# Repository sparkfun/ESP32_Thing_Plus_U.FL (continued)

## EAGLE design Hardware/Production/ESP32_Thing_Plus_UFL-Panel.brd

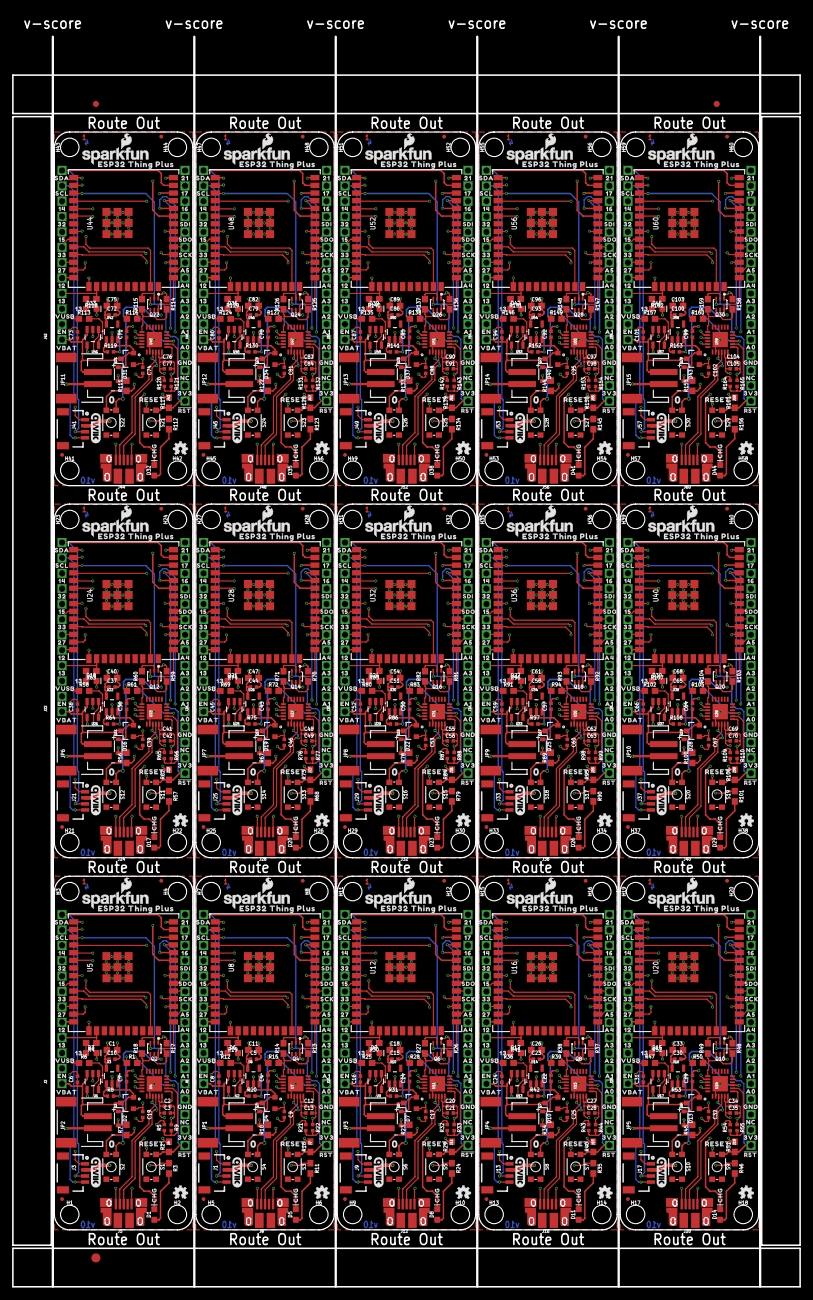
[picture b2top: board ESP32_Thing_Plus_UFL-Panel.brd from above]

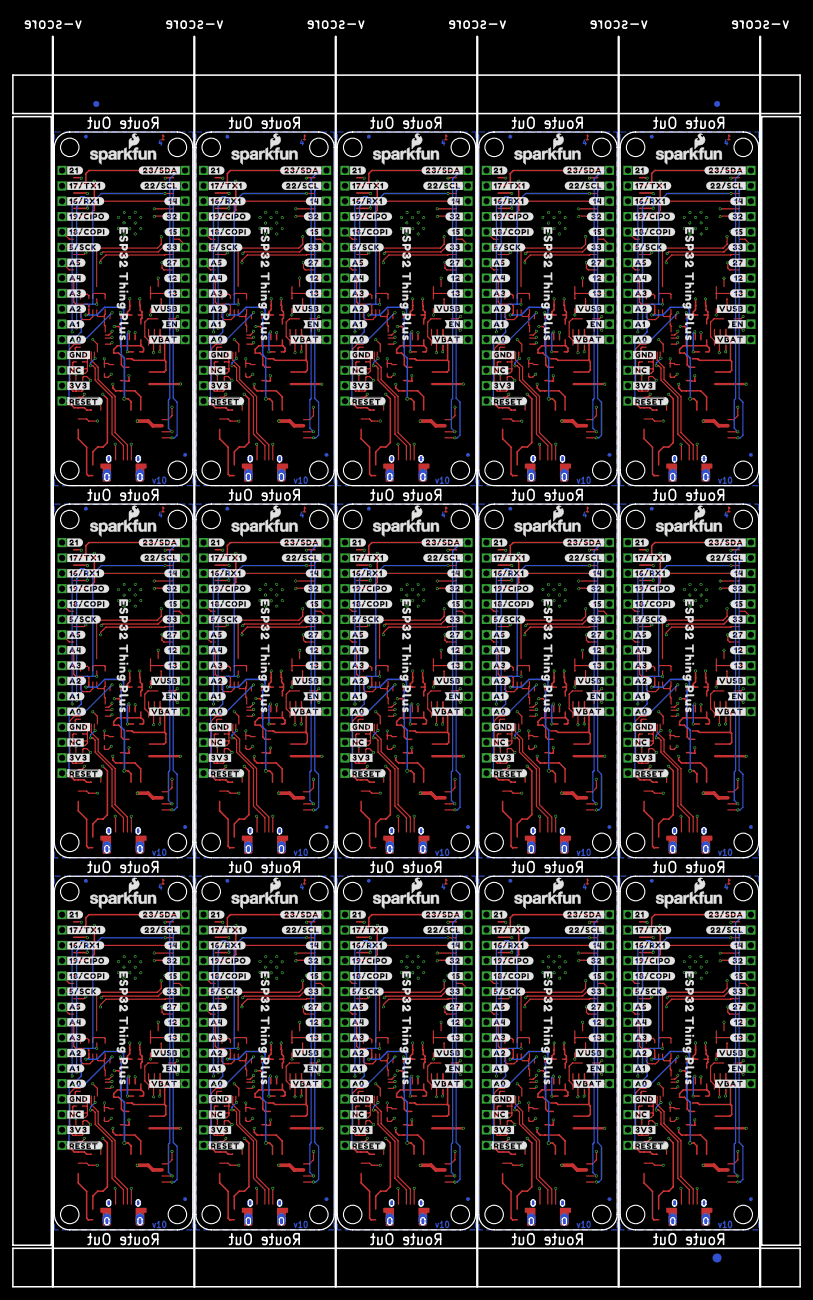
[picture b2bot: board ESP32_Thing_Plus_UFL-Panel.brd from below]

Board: 4 copper layers, 130.0 x 206.5 mm, 1671 parts (483 on the bottom side), 645 nets.

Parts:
C1, C11, C18, C26, C33, C40, C47, C54, C61, C68, C75, C82, C89, C96, C103: 10uF; 0603
C2, C12, C20, C27, C34, C41, C48, C55, C62, C69, C76, C83, C90, C97, C104: 0.1uF; 0402-TIGHT
C3, C6, C8, C9, C13, C16, C17, C19, C21, C24, C25, C28, C31, C32, C35, C38, C39, C42, C45, C46, C49, C52, C53, C56, C59, C60, C63, C66, C67, C70, C73, C74, C77, C80, C81, C84, C87, C88, C91, C94, C95, C98, C101, C102, C105: 4.7uF; 0402-TIGHT
C4, C5, C7, C10, C14, C15, C22, C23, C29, C30, C36, C37, C43, C44, C50, C51, C57, C58, C64, C65, C71, C72, C78, C79, C85, C86, C92, C93, C99, C100: 1.0uF; 0402-TIGHT
D1, D5, D8, D11, D14, D17, D20, D23, D26, D29, D32, D35, D38, D41, D44: Yellow; LED-0603
D2, D4, D7, D10, D13, D16, D19, D22, D25, D28, D31, D34, D37, D40, D43: 1A/23V/620mV; SOD-323
D3, D6, D9, D12, D15, D18, D21, D24, D27, D30, D33, D36, D39, D42, D45: BLUE; LED-0603
E$1, E$2, E$3, E$4: FIDUCIAL-1X2
E$5, E$6: FIDUCIAL-1.5X3
FD1, FD2, FD3, FD4, FD5, FD6, FD7, FD8, FD9, FD10, FD11, FD12, FD13, FD14, FD15, FD16, FD17, FD18, FD19, FD20, FD21, FD22, FD23, FD24, FD25, FD26, FD27, FD28, FD29, FD30, FD31, FD32, FD33, FD34, FD35, FD36, FD37, FD38, FD39, FD40, FD41, FD42, FD43, FD44, FD45, FD46, FD47, FD48, FD49, FD50, FD51, FD52, FD53, FD54, FD55, FD56, FD57, FD58, FD59, FD60: FIDUCIALUFIDUCIAL; FIDUCIAL-MICRO
H1, H2, H3, H4, H5, H6, H7, H8, H9, H10, H11, H12, H13, H14, H15, H16, H17, H18, H19, H20, H21, H22, H23, H24, H25, H26, H27, H28, H29, H30, H31, H32, H33, H34, H35, H36, H37, H38, H39, H40, H41, H42, H43, H44, H45, H46, H47, H48, H49, H50, H51, H52, H53, H54, H55, H56, H57, H58, H59, H60: STAND-OFFTIGHT; STAND-OFF-TIGHT
J1, J3, J9, J13, J17, J21, J25, J29, J33, J37, J41, J45, J49, J53, J57: 1X04_1MM_RA
J2, J6, J10, J14, J18, J22, J26, J30, J34, J38, J42, J46, J50, J54, J58: 1X12_SM_SQ_NOSILK
J4, J7, J11, J15, J19, J23, J27, J31, J35, J39, J43, J47, J51, J55, J59: 1X16_SM_SQ_NOSILK
J5, J8, J12, J16, J20, J24, J28, J32, J36, J40, J44, J48, J52, J56, J60: USB-MICROB-PTH-MILL
JP1, JP2, JP3, JP4, JP5, JP6, JP7, JP8, JP9, JP10, JP11, JP12, JP13, JP14, JP15: LiPo; JST-2-SMD
LOGO1, LOGO2, LOGO11, LOGO16, LOGO21, LOGO26, LOGO31, LOGO36, LOGO41, LOGO46, LOGO51, LOGO56, LOGO61, LOGO66, LOGO71: OSHW-LOGOMINI; OSHW-LOGO-MINI
LOGO3, LOGO5, LOGO7, LOGO9, LOGO12, LOGO14, LOGO17, LOGO19, LOGO22, LOGO24, LOGO27, LOGO29, LOGO32, LOGO34, LOGO37, LOGO39, LOGO42, LOGO44, LOGO47, LOGO49, LOGO52, LOGO54, LOGO57, LOGO59, LOGO62, LOGO64, LOGO67, LOGO69, LOGO72, LOGO74: SFE_LOGO_NAME_FLAME.1_INCH; SFE_LOGO_NAME_FLAME_.1
LOGO4, LOGO8, LOGO13, LOGO18, LOGO23, LOGO28, LOGO33, LOGO38, LOGO43, LOGO48, LOGO53, LOGO58, LOGO63, LOGO68, LOGO73: FOUR_LAYER_WARNING
LOGO6, LOGO10, LOGO15, LOGO20, LOGO25, LOGO30, LOGO35, LOGO40, LOGO45, LOGO50, LOGO55, LOGO60, LOGO65, LOGO70, LOGO75: QWIIC_LOGO_5MM; QWIIC_5MM
Q1, Q3, Q5, Q7, Q9, Q11, Q13, Q15, Q17, Q19, Q21, Q23, Q25, Q27, Q29: 2.5A/30V; SOT23-3@1
Q2, Q4, Q6, Q8, Q10, Q12, Q14, Q16, Q18, Q20, Q22, Q24, Q26, Q28, Q30: MBT3904DW1T1; SC70-6
R1, R2, R7, R10, R13, R14, R15, R16, R17, R18, R23, R26, R27, R28, R29, R34, R37, R38, R39, R40, R45, R48, R49, R50, R51, R56, R59, R60, R61, R62, R67, R70, R71, R72, R73, R78, R81, R82, R83, R84, R89, R92, R93, R94, R95, R100, R103, R104, R105, R106, R111, R114, R115, R116, R117, R122, R125, R126, R127, R128, R133, R136, R137, R138, R139, R144, R147, R148, R149, R150, R155, R158, R159, R160, R161: 10k; 0603
R3, R11, R24, R35, R46, R57, R68, R79, R90, R101, R112, R123, R134, R145, R156: 1K; 0603
R4, R19, R30, R41, R52, R63, R74, R85, R96, R107, R118, R129, R140, R151, R162: 1k; 0603
R5, R21, R32, R43, R54, R65, R76, R87, R98, R109, R120, R131, R142, R153, R164: 22k; 0402-TIGHT
R6, R12, R25, R36, R47, R58, R69, R80, R91, R102, R113, R124, R135, R146, R157: 2.0k; 0603
R8, R20, R31, R42, R53, R64, R75, R86, R97, R108, R119, R130, R141, R152, R163: 100k; 0402-TIGHT
R9, R22, R33, R44, R55, R66, R77, R88, R99, R110, R121, R132, R143, R154, R165: 33k; 0402-TIGHT
S1, S3, S5, S7, S9, S11, S13, S15, S17, S19, S21, S23, S25, S27, S29: RESET; TACTILE_SWITCH_SMD_4.6X2.8MM
S2, S4, S6, S8, S10, S12, S14, S16, S18, S20, S22, S24, S26, S28, S30: 0; TACTILE_SWITCH_SMD_4.6X2.8MM
TP1, TP2, TP3, TP4, TP5, TP6, TP7, TP8, TP9, TP10, TP11, TP12, TP13, TP14, TP15: TP_15TH
U1, U2, U9, U13, U17, U21, U25, U29, U33, U37, U41, U45, U49, U53, U57: MCP73831; SOT23-5
U3, U6, U10, U14, U18, U22, U26, U30, U34, U38, U42, U46, U50, U54, U58: AP2112K-3.3V; SOT23-5
U4, U7, U11, U15, U19, U23, U27, U31, U35, U39, U43, U47, U51, U55, U59: CP210X; QFN24
U5, U8, U12, U16, U20, U24, U28, U32, U36, U40, U44, U48, U52, U56, U60: ESP-WROOM-32EU; ESP-WROOM-32EU-NARROW
U$1, U$123, U$186, U$249, U$312, U$375, U$438, U$501, U$564, U$627, U$690, U$753, U$816, U$879, U$942: ESP32_THING_PLUS_0
U$2, U$124, U$187, U$250, U$313, U$376, U$439, U$502, U$565, U$628, U$691, U$754, U$817, U$880, U$943: SDI0
U$3, U$107, U$170, U$233, U$296, U$359, U$422, U$485, U$548, U$611, U$674, U$737, U$800, U$863, U$926: #21#0
U$4, U$108, U$171, U$234, U$297, U$360, U$423, U$486, U$549, U$612, U$675, U$738, U$801, U$864, U$927: #17#TX1#0
U$5, U$109, U$172, U$235, U$298, U$361, U$424, U$487, U$550, U$613, U$676, U$739, U$802, U$865, U$928: #16#RX1#0
U$6, U$125, U$188, U$251, U$314, U$377, U$440, U$503, U$566, U$629, U$692, U$755, U$818, U$881, U$944: SDO0
U$7, U$126, U$189, U$252, U$315, U$378, U$441, U$504, U$567, U$630, U$693, U$756, U$819, U$882, U$945: #RST#0
U$8, U$110, U$173, U$236, U$299, U$362, U$425, U$488, U$551, U$614, U$677, U$740, U$803, U$866, U$929: #19#CIPO#0
U$9, U$59, U$127, U$190, U$253, U$316, U$379, U$442, U$505, U$568, U$631, U$694, U$757, U$820, U$883: ORDERING_INSTRUCTIONS
U$10, U$111, U$174, U$237, U$300, U$363, U$426, U$489, U$552, U$615, U$678, U$741, U$804, U$867, U$930: #18#COPI#0
U$11, U$112, U$175, U$238, U$301, U$364, U$427, U$490, U$553, U$616, U$679, U$742, U$805, U$868, U$931: #5#SCK#0
U$12, U$113, U$176, U$239, U$302, U$365, U$428, U$491, U$554, U$617, U$680, U$743, U$806, U$869, U$932: #A5#0
U$13, U$24, U$128, U$191, U$254, U$317, U$380, U$443, U$506, U$569, U$632, U$695, U$758, U$821, U$884: ESP32_THING_PLUS0
U$14, U$25, U$129, U$192, U$255, U$318, U$381, U$444, U$507, U$570, U$633, U$696, U$759, U$822, U$885: SDA0
U$15, U$26, U$130, U$193, U$256, U$319, U$382, U$445, U$508, U$571, U$634, U$697, U$760, U$823, U$886: SCL0
U$16, U$58, U$131, U$194, U$257, U$320, U$383, U$446, U$509, U$572, U$635, U$698, U$761, U$824, U$887: 140
U$17, U$68, U$132, U$195, U$258, U$321, U$384, U$447, U$510, U$573, U$636, U$699, U$762, U$825, U$888: 320
U$18, U$69, U$133, U$196, U$259, U$322, U$385, U$448, U$511, U$574, U$637, U$700, U$763, U$826, U$889: 150
U$19, U$114, U$177, U$240, U$303, U$366, U$429, U$492, U$555, U$618, U$681, U$744, U$807, U$870, U$933: #A4#0
U$20, U$70, U$134, U$197, U$260, U$323, U$386, U$449, U$512, U$575, U$638, U$701, U$764, U$827, U$890: 330
U$21, U$115, U$178, U$241, U$304, U$367, U$430, U$493, U$556, U$619, U$682, U$745, U$808, U$871, U$934: #A3#0
U$22, U$116, U$179, U$242, U$305, U$368, U$431, U$494, U$557, U$620, U$683, U$746, U$809, U$872, U$935: #A2#0
U$23, U$71, U$135, U$198, U$261, U$324, U$387, U$450, U$513, U$576, U$639, U$702, U$765, U$828, U$891: 270
U$27, U$117, U$180, U$243, U$306, U$369, U$432, U$495, U$558, U$621, U$684, U$747, U$810, U$873, U$936: #A1#0
U$28, U$118, U$181, U$244, U$307, U$370, U$433, U$496, U$559, U$622, U$685, U$748, U$811, U$874, U$937: #A0#0
U$29, U$72, U$136, U$199, U$262, U$325, U$388, U$451, U$514, U$577, U$640, U$703, U$766, U$829, U$892: 120
U$30, U$47, U$73, U$74, U$137, U$138, U$200, U$201, U$263, U$264, U$326, U$327, U$389, U$390, U$452, U$453, U$515, U$516, U$578, U$579, U$641, U$642, U$704, U$705, U$767, U$768, U$830, U$831, U$893, U$894: 130
U$31, U$91, U$158, U$221, U$284, U$347, U$410, U$473, U$536, U$599, U$662, U$725, U$788, U$851, U$914: #23#SDA#0
U$32, U$119, U$182, U$245, U$308, U$371, U$434, U$497, U$560, U$623, U$686, U$749, U$812, U$875, U$938: #GND#0
U$33, U$92, U$159, U$222, U$285, U$348, U$411, U$474, U$537, U$600, U$663, U$726, U$789, U$852, U$915: #22#SCL#0
U$34, U$97, U$160, U$223, U$286, U$349, U$412, U$475, U$538, U$601, U$664, U$727, U$790, U$853, U$916: #14#0
U$35, U$98, U$161, U$224, U$287, U$350, U$413, U$476, U$539, U$602, U$665, U$728, U$791, U$854, U$917: #32#0
U$36, U$99, U$162, U$225, U$288, U$351, U$414, U$477, U$540, U$603, U$666, U$729, U$792, U$855, U$918: #15#0
U$37, U$100, U$163, U$226, U$289, U$352, U$415, U$478, U$541, U$604, U$667, U$730, U$793, U$856, U$919: #33#0
U$38, U$101, U$164, U$227, U$290, U$353, U$416, U$479, U$542, U$605, U$668, U$731, U$794, U$857, U$920: #27#0
U$39, U$102, U$165, U$228, U$291, U$354, U$417, U$480, U$543, U$606, U$669, U$732, U$795, U$858, U$921: #12#0
U$40, U$103, U$166, U$229, U$292, U$355, U$418, U$481, U$544, U$607, U$670, U$733, U$796, U$859, U$922: #13#0
U$41, U$104, U$167, U$230, U$293, U$356, U$419, U$482, U$545, U$608, U$671, U$734, U$797, U$860, U$923: #VUSB#0
U$42, U$105, U$168, U$231, U$294, U$357, U$420, U$483, U$546, U$609, U$672, U$735, U$798, U$861, U$924: #VBAT#0
U$43, U$106, U$169, U$232, U$295, U$358, U$421, U$484, U$547, U$610, U$673, U$736, U$799, U$862, U$925: #EN#0
U$44, U$120, U$183, U$246, U$309, U$372, U$435, U$498, U$561, U$624, U$687, U$750, U$813, U$876, U$939: #NC#0
U$45, U$121, U$184, U$247, U$310, U$373, U$436, U$499, U$562, U$625, U$688, U$751, U$814, U$877, U$940: #3V3#0
U$46, U$122, U$185, U$248, U$311, U$374, U$437, U$500, U$563, U$626, U$689, U$752, U$815, U$878, U$941: ##RESET##0
U$48, U$75, U$139, U$202, U$265, U$328, U$391, U$454, U$517, U$580, U$643, U$706, U$769, U$832, U$895: VUSB0
U$49, U$76, U$140, U$203, U$266, U$329, U$392, U$455, U$518, U$581, U$644, U$707, U$770, U$833, U$896: EN0
U$50, U$77, U$141, U$204, U$267, U$330, U$393, U$456, U$519, U$582, U$645, U$708, U$771, U$834, U$897: VBAT0
U$51, U$78, U$142, U$205, U$268, U$331, U$394, U$457, U$520, U$583, U$646, U$709, U$772, U$835, U$898: CHG0
U$52, U$79, U$143, U$206, U$269, U$332, U$395, U$458, U$521, U$584, U$647, U$710, U$773, U$836, U$899: RESET0
U$53, U$81, U$144, U$207, U$270, U$333, U$396, U$459, U$522, U$585, U$648, U$711, U$774, U$837, U$900: 3V30
U$54, U$82, U$145, U$208, U$271, U$334, U$397, U$460, U$523, U$586, U$649, U$712, U$775, U$838, U$901: NC0
U$55, U$83, U$146, U$209, U$272, U$335, U$398, U$461, U$524, U$587, U$650, U$713, U$776, U$839, U$902: GND0
U$56, U$84, U$147, U$210, U$273, U$336, U$399, U$462, U$525, U$588, U$651, U$714, U$777, U$840, U$903: A00
U$57, U$85, U$148, U$211, U$274, U$337, U$400, U$463, U$526, U$589, U$652, U$715, U$778, U$841, U$904: A10
U$60, U$86, U$149, U$212, U$275, U$338, U$401, U$464, U$527, U$590, U$653, U$716, U$779, U$842, U$905: A20
U$61, U$87, U$150, U$213, U$276, U$339, U$402, U$465, U$528, U$591, U$654, U$717, U$780, U$843, U$906: A30
U$62, U$88, U$151, U$214, U$277, U$340, U$403, U$466, U$529, U$592, U$655, U$718, U$781, U$844, U$907: A40
U$63, U$89, U$152, U$215, U$278, U$341, U$404, U$467, U$530, U$593, U$656, U$719, U$782, U$845, U$908: A50
U$64, U$90, U$153, U$216, U$279, U$342, U$405, U$468, U$531, U$594, U$657, U$720, U$783, U$846, U$909: SCK0
U$65, U$93, U$154, U$217, U$280, U$343, U$406, U$469, U$532, U$595, U$658, U$721, U$784, U$847, U$910: 160
U$66, U$94, U$155, U$218, U$281, U$344, U$407, U$470, U$533, U$596, U$659, U$722, U$785, U$848, U$911: 170
U$67, U$95, U$156, U$219, U$282, U$345, U$408, U$471, U$534, U$597, U$660, U$723, U$786, U$849, U$912: 210
U$80, U$96, U$157, U$220, U$283, U$346, U$409, U$472, U$535, U$598, U$661, U$724, U$787, U$850, U$913: 00

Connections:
0: Q2.6, S2.4, TP1.P$1, U5.25
1: Q4.6, S4.4, TP2.P$1, U8.25
2: J6.10, U8.13
3: J6.9, U8.8
3.3V: C1.1, C2.1, C3.1, C10.1, J3.2, J4.2, R1.1, R2.2, U3.5, U4.5, U4.6, U4.7, U5.2
3.3V1: C5.1, C11.1, C12.1, C13.1, J1.2, J7.2, R15.1, R16.2, U6.5, U7.5, U7.6, U7.7, U8.2
3.3V2: C15.1, C18.1, C20.1, C21.1, J9.2, J11.2, R28.1, R29.2, U10.5, U11.5, U11.6, U11.7, U12.2
3.3V3: C23.1, C26.1, C27.1, C28.1, J13.2, J15.2, R39.1, R40.2, U14.5, U15.5, U15.6, U15.7, U16.2
3.3V4: C30.1, C33.1, C34.1, C35.1, J17.2, J19.2, R50.1, R51.2, U18.5, U19.5, U19.6, U19.7, U20.2
3.3V5: C37.1, C40.1, C41.1, C42.1, J21.2, J23.2, R61.1, R62.2, U22.5, U23.5, U23.6, U23.7, U24.2
3.3V6: C44.1, C47.1, C48.1, C49.1, J25.2, J27.2, R72.1, R73.2, U26.5, U27.5, U27.6, U27.7, U28.2
3.3V7: C51.1, C54.1, C55.1, C56.1, J29.2, J31.2, R83.1, R84.2, U30.5, U31.5, U31.6, U31.7, U32.2
3.3V8: C58.1, C61.1, C62.1, C63.1, J33.2, J35.2, R94.1, R95.2, U34.5, U35.5, U35.6, U35.7, U36.2
3.3V9: C65.1, C68.1, C69.1, C70.1, J37.2, J39.2, R105.1, R106.2, U38.5, U39.5, U39.6, U39.7, U40.2
3.3V10: C72.1, C75.1, C76.1, C77.1, J41.2, J43.2, R116.1, R117.2, U42.5, U43.5, U43.6, U43.7, U44.2
3.3V11: C79.1, C82.1, C83.1, C84.1, J45.2, J47.2, R127.1, R128.2, U46.5, U47.5, U47.6, U47.7, U48.2
3.3V12: C86.1, C89.1, C90.1, C91.1, J49.2, J51.2, R138.1, R139.2, U50.5, U51.5, U51.6, U51.7, U52.2
3.3V13: C93.1, C96.1, C97.1, C98.1, J53.2, J55.2, R149.1, R150.2, U54.5, U55.5, U55.6, U55.7, U56.2
3.3V14: C100.1, C103.1, C104.1, C105.1, J57.2, J59.2, R160.1, R161.2, U58.5, U59.5, U59.6, U59.7, U60.2
4: J6.8, U8.23
5: J6.7, U8.9
6: J6.6, U8.12
7: J6.5, U8.14
8: J6.4, R19.1, U8.16
9: J7.14, U8.27
10: J7.15, U8.28
11: J7.16, U8.33
12: J2.5, U5.14
13: J2.4, R4.1, U5.16
14: J2.10, U5.13
15: J2.8, U5.23
16: J4.14, U5.27
17: J4.15, U5.28
18: Q6.6, S6.4, TP3.P$1, U12.25
19: J10.10, U12.13
20: J10.9, U12.8
21: J4.16, U5.33
22: J10.8, U12.23
23: J10.7, U12.9
24: J10.6, U12.12
25: J10.5, U12.14
26: J10.4, R30.1, U12.16
27: J2.6, U5.12
28: J11.14, U12.27
29: J11.15, U12.28
30: J11.16, U12.33
31: Q8.6, S8.4, TP4.P$1, U16.25
32: J2.9, U5.8
33: J2.7, U5.9
34: J14.10, U16.13
35: J14.9, U16.8
36: J14.8, U16.23
37: J14.7, U16.9
38: J14.6, U16.12
39: J14.5, U16.14
40: J14.4, R41.1, U16.16
41: J15.14, U16.27
42: J15.15, U16.28
43: J15.16, U16.33
44: Q10.6, S10.4, TP5.P$1, U20.25
45: J18.10, U20.13
46: J18.9, U20.8
47: J18.8, U20.23
48: J18.7, U20.9
49: J18.6, U20.12
50: J18.5, U20.14
51: J18.4, R52.1, U20.16
52: J19.14, U20.27
53: J19.15, U20.28
54: J19.16, U20.33
55: Q12.6, S12.4, TP6.P$1, U24.25
56: J22.10, U24.13
57: J22.9, U24.8
58: J22.8, U24.23
59: J22.7, U24.9
60: J22.6, U24.12
61: J22.5, U24.14
62: J22.4, R63.1, U24.16
63: J23.14, U24.27
64: J23.15, U24.28
65: J23.16, U24.33
66: Q14.6, S14.4, TP7.P$1, U28.25
67: J26.10, U28.13
68: J26.9, U28.8
69: J26.8, U28.23
70: J26.7, U28.9
71: J26.6, U28.12
72: J26.5, U28.14
73: J26.4, R74.1, U28.16
74: J27.14, U28.27
75: J27.15, U28.28
76: J27.16, U28.33
77: Q16.6, S16.4, TP8.P$1, U32.25
78: J30.10, U32.13
79: J30.9, U32.8
80: J30.8, U32.23
81: J30.7, U32.9
82: J30.6, U32.12
83: J30.5, U32.14
84: J30.4, R85.1, U32.16
85: J31.14, U32.27
86: J31.15, U32.28
87: J31.16, U32.33
88: Q18.6, S18.4, TP9.P$1, U36.25
89: J34.10, U36.13
90: J34.9, U36.8
91: J34.8, U36.23
92: J34.7, U36.9
93: J34.6, U36.12
94: J34.5, U36.14
95: J34.4, R96.1, U36.16
96: J35.14, U36.27
97: J35.15, U36.28
98: J35.16, U36.33
99: Q20.6, S20.4, TP10.P$1, U40.25
100: J38.10, U40.13
101: J38.9, U40.8
102: J38.8, U40.23
103: J38.7, U40.9
104: J38.6, U40.12
105: J38.5, U40.14
106: J38.4, R107.1, U40.16
107: J39.14, U40.27
108: J39.15, U40.28
109: J39.16, U40.33
110: Q22.6, S22.4, TP11.P$1, U44.25
111: J42.10, U44.13
112: J42.9, U44.8
113: J42.8, U44.23
114: J42.7, U44.9
115: J42.6, U44.12
116: J42.5, U44.14
117: J42.4, R118.1, U44.16
118: J43.14, U44.27
119: J43.15, U44.28
120: J43.16, U44.33
121: Q24.6, S24.4, TP12.P$1, U48.25
122: J46.10, U48.13
123: J46.9, U48.8
124: J46.8, U48.23
125: J46.7, U48.9
126: J46.6, U48.12
127: J46.5, U48.14
128: J46.4, R129.1, U48.16
129: J47.14, U48.27
130: J47.15, U48.28
131: J47.16, U48.33
132: Q26.6, S26.4, TP13.P$1, U52.25
133: J50.10, U52.13
134: J50.9, U52.8
135: J50.8, U52.23
136: J50.7, U52.9
137: J50.6, U52.12
138: J50.5, U52.14
139: J50.4, R140.1, U52.16
140: J51.14, U52.27
141: J51.15, U52.28
142: J51.16, U52.33
143: Q28.6, S28.4, TP14.P$1, U56.25
144: J54.10, U56.13
145: J54.9, U56.8
146: J54.8, U56.23
147: J54.7, U56.9
148: J54.6, U56.12
149: J54.5, U56.14
150: J54.4, R151.1, U56.16
151: J55.14, U56.27
152: J55.15, U56.28
153: J55.16, U56.33
154: Q30.6, S30.4, TP15.P$1, U60.25
155: J58.10, U60.13
156: J58.9, U60.8
157: J58.8, U60.23
158: J58.7, U60.9
159: J58.6, U60.12
160: J58.5, U60.14
161: J58.4, R162.1, U60.16
162: J59.14, U60.27
163: J59.15, U60.28
164: J59.16, U60.33
A0: J4.5, U5.11
A1: J4.6, U5.10
A2: J4.7, U5.6
A3: J4.8, U5.5
A4: J4.9, U5.4
A5: J4.10, U5.26
A6: J7.5, U8.11
A7: J7.6, U8.10
A8: J7.7, U8.6
A9: J7.8, U8.5
A10: J7.9, U8.4
A11: J7.10, U8.26
A12: J11.5, U12.11
A13: J11.6, U12.10
A14: J11.7, U12.6
A15: J11.8, U12.5
A16: J11.9, U12.4
A17: J11.10, U12.26
A18: J15.5, U16.11
A19: J15.6, U16.10
A20: J15.7, U16.6
A21: J15.8, U16.5
A22: J15.9, U16.4
A23: J15.10, U16.26
A24: J19.5, U20.11
A25: J19.6, U20.10
A26: J19.7, U20.6
A27: J19.8, U20.5
A28: J19.9, U20.4
A29: J19.10, U20.26
A30: J23.5, U24.11
A31: J23.6, U24.10
A32: J23.7, U24.6
A33: J23.8, U24.5
A34: J23.9, U24.4
A35: J23.10, U24.26
A36: J27.5, U28.11
A37: J27.6, U28.10
A38: J27.7, U28.6
A39: J27.8, U28.5
A40: J27.9, U28.4
A41: J27.10, U28.26
A42: J31.5, U32.11
A43: J31.6, U32.10
A44: J31.7, U32.6
A45: J31.8, U32.5
A46: J31.9, U32.4
A47: J31.10, U32.26
A48: J35.5, U36.11
A49: J35.6, U36.10
A50: J35.7, U36.6
A51: J35.8, U36.5
A52: J35.9, U36.4
A53: J35.10, U36.26
A54: J39.5, U40.11
A55: J39.6, U40.10
A56: J39.7, U40.6
A57: J39.8, U40.5
A58: J39.9, U40.4
A59: J39.10, U40.26
A60: J43.5, U44.11
A61: J43.6, U44.10
A62: J43.7, U44.6
A63: J43.8, U44.5
A64: J43.9, U44.4
A65: J43.10, U44.26
A66: J47.5, U48.11
A67: J47.6, U48.10
A68: J47.7, U48.6
A69: J47.8, U48.5
A70: J47.9, U48.4
A71: J47.10, U48.26
A72: J51.5, U52.11
A73: J51.6, U52.10
A74: J51.7, U52.6
A75: J51.8, U52.5
A76: J51.9, U52.4
A77: J51.10, U52.26
A78: J55.5, U56.11
A79: J55.6, U56.10
A80: J55.7, U56.6
A81: J55.8, U56.5
A82: J55.9, U56.4
A83: J55.10, U56.26
A84: J59.5, U60.11
A85: J59.6, U60.10
A86: J59.7, U60.6
A87: J59.8, U60.5
A88: J59.9, U60.4
A89: J59.10, U60.26
CHG: D1.C, U1.1
CHG1: D5.C, U2.1
CHG2: D8.C, U9.1
CHG3: D11.C, U13.1
CHG4: D14.C, U17.1
CHG5: D17.C, U21.1
CHG6: D20.C, U25.1
CHG7: D23.C, U29.1
CHG8: D26.C, U33.1
CHG9: D29.C, U37.1
CHG10: D32.C, U41.1
CHG11: D35.C, U45.1
CHG12: D38.C, U49.1
CHG13: D41.C, U53.1
CHG14: D44.C, U57.1
CHIP_PU: J4.1, Q2.3, R2.1, S1.4, U5.3
CHIP_PU1: J7.1, Q4.3, R16.1, S3.4, U8.3
CHIP_PU2: J11.1, Q6.3, R29.1, S5.4, U12.3
CHIP_PU3: J15.1, Q8.3, R40.1, S7.4, U16.3
CHIP_PU4: J19.1, Q10.3, R51.1, S9.4, U20.3
CHIP_PU5: J23.1, Q12.3, R62.1, S11.4, U24.3
CHIP_PU6: J27.1, Q14.3, R73.1, S13.4, U28.3
CHIP_PU7: J31.1, Q16.3, R84.1, S15.4, U32.3
CHIP_PU8: J35.1, Q18.3, R95.1, S17.4, U36.3
CHIP_PU9: J39.1, Q20.3, R106.1, S19.4, U40.3
CHIP_PU10: J43.1, Q22.3, R117.1, S21.4, U44.3
CHIP_PU11: J47.1, Q24.3, R128.1, S23.4, U48.3
CHIP_PU12: J51.1, Q26.3, R139.1, S25.4, U52.3
CHIP_PU13: J55.1, Q28.3, R150.1, S27.4, U56.3
CHIP_PU14: J59.1, Q30.3, R161.1, S29.4, U60.3
CIPO: J4.13, U5.31
CIPO1: J7.13, U8.31
CIPO2: J11.13, U12.31
CIPO3: J15.13, U16.31
CIPO4: J19.13, U20.31
CIPO5: J23.13, U24.31
CIPO6: J27.13, U28.31
CIPO7: J31.13, U32.31
CIPO8: J35.13, U36.31
CIPO9: J39.13, U40.31
CIPO10: J43.13, U44.31
CIPO11: J47.13, U48.31
CIPO12: J51.13, U52.31
CIPO13: J55.13, U56.31
CIPO14: J59.13, U60.31
COPI: J4.12, U5.30
COPI1: J7.12, U8.30
COPI2: J11.12, U12.30
COPI3: J15.12, U16.30
COPI4: J19.12, U20.30
COPI5: J23.12, U24.30
COPI6: J27.12, U28.30
COPI7: J31.12, U32.30
COPI8: J35.12, U36.30
COPI9: J39.12, U40.30
COPI10: J43.12, U44.30
COPI11: J47.12, U48.30
COPI12: J51.12, U52.30
COPI13: J55.12, U56.30
COPI14: J59.12, U60.30
D+: J5.D+, U4.3
D+1: J8.D+, U7.3
D+2: J12.D+, U11.3
D+3: J16.D+, U15.3
D+4: J20.D+, U19.3
D+5: J24.D+, U23.3
D+6: J28.D+, U27.3
D+7: J32.D+, U31.3
D+8: J36.D+, U35.3
D+9: J40.D+, U39.3
D+10: J44.D+, U43.3
D+11: J48.D+, U47.3
D+12: J52.D+, U51.3
D+13: J56.D+, U55.3
D+14: J60.D+, U59.3
D-: J5.D-, U4.4
D-1: J8.D-, U7.4
D-2: J12.D-, U11.4
D-3: J16.D-, U15.4
D-4: J20.D-, U19.4
D-5: J24.D-, U23.4
D-6: J28.D-, U27.4
D-7: J32.D-, U31.4
D-8: J36.D-, U35.4
D-9: J40.D-, U39.4
D-10: J44.D-, U43.4
D-11: J48.D-, U47.4
D-12: J52.D-, U51.4
D-13: J56.D-, U55.4
D-14: J60.D-, U59.4
DTR: Q2.1, R17.1, U4.23
DTR1: Q4.1, R13.1, U7.23
DTR2: Q6.1, R26.1, U11.23
DTR3: Q8.1, R37.1, U15.23
DTR4: Q10.1, R48.1, U19.23
DTR5: Q12.1, R59.1, U23.23
DTR6: Q14.1, R70.1, U27.23
DTR7: Q16.1, R81.1, U31.23
DTR8: Q18.1, R92.1, U35.23
DTR9: Q20.1, R103.1, U39.23
DTR10: Q22.1, R114.1, U43.23
DTR11: Q24.1, R125.1, U47.23
DTR12: Q26.1, R136.1, U51.23
DTR13: Q28.1, R147.1, U55.23
DTR14: Q30.1, R158.1, U59.23
EN: J2.2, R8.2, U3.3
EN1: J6.2, R20.2, U6.3
EN2: J10.2, R31.2, U10.3
EN3: J14.2, R42.2, U14.3
EN4: J18.2, R53.2, U18.3
EN5: J22.2, R64.2, U22.3
EN6: J26.2, R75.2, U26.3
EN7: J30.2, R86.2, U30.3
EN8: J34.2, R97.2, U34.3
EN9: J38.2, R108.2, U38.3
EN10: J42.2, R119.2, U42.3
EN11: J46.2, R130.2, U46.3
EN12: J50.2, R141.2, U50.3
EN13: J54.2, R152.2, U54.3
EN14: J58.2, R163.2, U58.3
GND: C1.2, C2.2, C3.2, C6.2, C7.2, C10.2, C19.2, D3.C, J3.1, J4.4, J5.GND, JP2.1, R6.1, R7.1, R9.1, S1.1, S2.1, U1.2, U3.2, U4.2, U4.PAD, U5.1, U5.15, U5.38, U5.GND, U5.P$1, U5.P$2, U5.P$3, U5.P$4, U5.P$5, U5.P$6, U5.P$7, U5.P$8
GND1: C4.2, C5.2, C8.2, C9.2, C11.2, C12.2, C13.2, D6.C, J1.1, J7.4, J8.GND, JP1.1, R10.1, R12.1, R22.1, S3.1, S4.1, U2.2, U6.2, U7.2, U7.PAD, U8.1, U8.15, U8.38, U8.GND, U8.P$1, U8.P$2, U8.P$3, U8.P$4, U8.P$5, U8.P$6, U8.P$7, U8.P$8
GND2: C14.2, C15.2, C16.2, C17.2, C18.2, C20.2, C21.2, D9.C, J9.1, J11.4, J12.GND, JP3.1, R23.1, R25.1, R33.1, S5.1, S6.1, U9.2, U10.2, U11.2, U11.PAD, U12.1, U12.15, U12.38, U12.GND, U12.P$1, U12.P$2, U12.P$3, U12.P$4, U12.P$5, U12.P$6, U12.P$7, U12.P$8
GND3: C22.2, C23.2, C24.2, C25.2, C26.2, C27.2, C28.2, D12.C, J13.1, J15.4, J16.GND, JP4.1, R34.1, R36.1, R44.1, S7.1, S8.1, U13.2, U14.2, U15.2, U15.PAD, U16.1, U16.15, U16.38, U16.GND, U16.P$1, U16.P$2, U16.P$3, U16.P$4, U16.P$5, U16.P$6, U16.P$7, U16.P$8
GND4: C29.2, C30.2, C31.2, C32.2, C33.2, C34.2, C35.2, D15.C, J17.1, J19.4, J20.GND, JP5.1, R45.1, R47.1, R55.1, S9.1, S10.1, U17.2, U18.2, U19.2, U19.PAD, U20.1, U20.15, U20.38, U20.GND, U20.P$1, U20.P$2, U20.P$3, U20.P$4, U20.P$5, U20.P$6, U20.P$7, U20.P$8
GND5: C36.2, C37.2, C38.2, C39.2, C40.2, C41.2, C42.2, D18.C, J21.1, J23.4, J24.GND, JP6.1, R56.1, R58.1, R66.1, S11.1, S12.1, U21.2, U22.2, U23.2, U23.PAD, U24.1, U24.15, U24.38, U24.GND, U24.P$1, U24.P$2, U24.P$3, U24.P$4, U24.P$5, U24.P$6, U24.P$7, U24.P$8
GND6: C43.2, C44.2, C45.2, C46.2, C47.2, C48.2, C49.2, D21.C, J25.1, J27.4, J28.GND, JP7.1, R67.1, R69.1, R77.1, S13.1, S14.1, U25.2, U26.2, U27.2, U27.PAD, U28.1, U28.15, U28.38, U28.GND, U28.P$1, U28.P$2, U28.P$3, U28.P$4, U28.P$5, U28.P$6, U28.P$7, U28.P$8
GND7: C50.2, C51.2, C52.2, C53.2, C54.2, C55.2, C56.2, D24.C, J29.1, J31.4, J32.GND, JP8.1, R78.1, R80.1, R88.1, S15.1, S16.1, U29.2, U30.2, U31.2, U31.PAD, U32.1, U32.15, U32.38, U32.GND, U32.P$1, U32.P$2, U32.P$3, U32.P$4, U32.P$5, U32.P$6, U32.P$7, U32.P$8
GND8: C57.2, C58.2, C59.2, C60.2, C61.2, C62.2, C63.2, D27.C, J33.1, J35.4, J36.GND, JP9.1, R89.1, R91.1, R99.1, S17.1, S18.1, U33.2, U34.2, U35.2, U35.PAD, U36.1, U36.15, U36.38, U36.GND, U36.P$1, U36.P$2, U36.P$3, U36.P$4, U36.P$5, U36.P$6, U36.P$7, U36.P$8
GND9: C64.2, C65.2, C66.2, C67.2, C68.2, C69.2, C70.2, D30.C, J37.1, J39.4, J40.GND, JP10.1, R100.1, R102.1, R110.1, S19.1, S20.1, U37.2, U38.2, U39.2, U39.PAD, U40.1, U40.15, U40.38, U40.GND, U40.P$1, U40.P$2, U40.P$3, U40.P$4, U40.P$5, U40.P$6, U40.P$7, U40.P$8
GND10: C71.2, C72.2, C73.2, C74.2, C75.2, C76.2, C77.2, D33.C, J41.1, J43.4, J44.GND, JP11.1, R111.1, R113.1, R121.1, S21.1, S22.1, U41.2, U42.2, U43.2, U43.PAD, U44.1, U44.15, U44.38, U44.GND, U44.P$1, U44.P$2, U44.P$3, U44.P$4, U44.P$5, U44.P$6, U44.P$7, U44.P$8
GND11: C78.2, C79.2, C80.2, C81.2, C82.2, C83.2, C84.2, D36.C, J45.1, J47.4, J48.GND, JP12.1, R122.1, R124.1, R132.1, S23.1, S24.1, U45.2, U46.2, U47.2, U47.PAD, U48.1, U48.15, U48.38, U48.GND, U48.P$1, U48.P$2, U48.P$3, U48.P$4, U48.P$5, U48.P$6, U48.P$7, U48.P$8
GND12: C85.2, C86.2, C87.2, C88.2, C89.2, C90.2, C91.2, D39.C, J49.1, J51.4, J52.GND, JP13.1, R133.1, R135.1, R143.1, S25.1, S26.1, U49.2, U50.2, U51.2, U51.PAD, U52.1, U52.15, U52.38, U52.GND, U52.P$1, U52.P$2, U52.P$3, U52.P$4, U52.P$5, U52.P$6, U52.P$7, U52.P$8
GND13: C92.2, C93.2, C94.2, C95.2, C96.2, C97.2, C98.2, D42.C, J53.1, J55.4, J56.GND, JP14.1, R144.1, R146.1, R154.1, S27.1, S28.1, U53.2, U54.2, U55.2, U55.PAD, U56.1, U56.15, U56.38, U56.GND, U56.P$1, U56.P$2, U56.P$3, U56.P$4, U56.P$5, U56.P$6, U56.P$7, U56.P$8
GND14: C99.2, C100.2, C101.2, C102.2, C103.2, C104.2, C105.2, D45.C, J57.1, J59.4, J60.GND, JP15.1, R155.1, R157.1, R165.1, S29.1, S30.1, U57.2, U58.2, U59.2, U59.PAD, U60.1, U60.15, U60.38, U60.GND, U60.P$1, U60.P$2, U60.P$3, U60.P$4, U60.P$5, U60.P$6, U60.P$7, U60.P$8
unnamed: R1.2, U4.9
unnamed: D3.A, R4.2
unnamed: R12.2, U2.5
unnamed: R5.1, R9.2, U4.8
unnamed: Q4.5, R13.2
unnamed: Q4.2, R14.2
unnamed: D5.A, R11.2
unnamed: R15.2, U7.9
unnamed: D6.A, R19.2
unnamed: Q2.5, R17.2
unnamed: R21.1, R22.2, U7.8
unnamed: Q2.2, R18.2
unnamed: R25.2, U9.5
unnamed: R6.2, U1.5
unnamed: Q6.5, R26.2
unnamed: Q6.2, R27.2
unnamed: D1.A, R3.2
unnamed: D8.A, R24.2
unnamed: R28.2, U11.9
unnamed: D9.A, R30.2
unnamed: R32.1, R33.2, U11.8
unnamed: R36.2, U13.5
unnamed: Q8.5, R37.2
unnamed: Q8.2, R38.2
unnamed: D11.A, R35.2
unnamed: R39.2, U15.9
unnamed: D12.A, R41.2
unnamed: R43.1, R44.2, U15.8
unnamed: R47.2, U17.5
unnamed: Q10.5, R48.2
unnamed: Q10.2, R49.2
unnamed: D14.A, R46.2
unnamed: R50.2, U19.9
unnamed: D15.A, R52.2
unnamed: R54.1, R55.2, U19.8
unnamed: R58.2, U21.5
unnamed: Q12.5, R59.2
unnamed: Q12.2, R60.2
unnamed: D17.A, R57.2
unnamed: R61.2, U23.9
unnamed: D18.A, R63.2
unnamed: R65.1, R66.2, U23.8
unnamed: R69.2, U25.5
unnamed: Q14.5, R70.2
unnamed: Q14.2, R71.2
unnamed: D20.A, R68.2
unnamed: R72.2, U27.9
unnamed: D21.A, R74.2
unnamed: R76.1, R77.2, U27.8
unnamed: R80.2, U29.5
unnamed: Q16.5, R81.2
unnamed: Q16.2, R82.2
unnamed: D23.A, R79.2
unnamed: R83.2, U31.9
unnamed: D24.A, R85.2
unnamed: R87.1, R88.2, U31.8
unnamed: R91.2, U33.5
unnamed: Q18.5, R92.2
unnamed: Q18.2, R93.2
unnamed: D26.A, R90.2
unnamed: R94.2, U35.9
unnamed: D27.A, R96.2
unnamed: R98.1, R99.2, U35.8
unnamed: R102.2, U37.5
unnamed: Q20.5, R103.2
unnamed: Q20.2, R104.2
unnamed: D29.A, R101.2
unnamed: R105.2, U39.9
unnamed: D30.A, R107.2
unnamed: R109.1, R110.2, U39.8
unnamed: R113.2, U41.5
unnamed: Q22.5, R114.2
unnamed: Q22.2, R115.2
unnamed: D32.A, R112.2
unnamed: R116.2, U43.9
unnamed: D33.A, R118.2
unnamed: R120.1, R121.2, U43.8
unnamed: R124.2, U45.5
unnamed: Q24.5, R125.2
unnamed: Q24.2, R126.2
unnamed: D35.A, R123.2
unnamed: R127.2, U47.9
unnamed: D36.A, R129.2
unnamed: R131.1, R132.2, U47.8
unnamed: R135.2, U49.5
unnamed: Q26.5, R136.2
unnamed: Q26.2, R137.2
unnamed: D38.A, R134.2
unnamed: R138.2, U51.9
unnamed: D39.A, R140.2
unnamed: R142.1, R143.2, U51.8
unnamed: R146.2, U53.5
unnamed: Q28.5, R147.2
unnamed: Q28.2, R148.2
unnamed: D41.A, R145.2
unnamed: R149.2, U55.9
unnamed: D42.A, R151.2
unnamed: R153.1, R154.2, U55.8
unnamed: R157.2, U57.5
unnamed: Q30.5, R158.2
unnamed: Q30.2, R159.2
unnamed: D44.A, R156.2
unnamed: R160.2, U59.9
unnamed: D45.A, R162.2
unnamed: R164.1, R165.2, U59.8
RTS: Q2.4, R18.1, U4.19
RTS1: Q4.4, R14.1, U7.19
RTS2: Q6.4, R27.1, U11.19
RTS3: Q8.4, R38.1, U15.19
RTS4: Q10.4, R49.1, U19.19
RTS5: Q12.4, R60.1, U23.19
RTS6: Q14.4, R71.1, U27.19
RTS7: Q16.4, R82.1, U31.19
RTS8: Q18.4, R93.1, U35.19
RTS9: Q20.4, R104.1, U39.19
RTS10: Q22.4, R115.1, U43.19
RTS11: Q24.4, R126.1, U47.19
RTS12: Q26.4, R137.1, U51.19
RTS13: Q28.4, R148.1, U55.19
RTS14: Q30.4, R159.1, U59.19
RX: U4.20, U5.35
RX1: U7.20, U8.35
RX2: U11.20, U12.35
RX3: U15.20, U16.35
RX4: U19.20, U20.35
RX5: U23.20, U24.35
RX6: U27.20, U28.35
RX7: U31.20, U32.35
RX8: U35.20, U36.35
RX9: U39.20, U40.35
RX10: U43.20, U44.35
RX11: U47.20, U48.35
RX12: U51.20, U52.35
RX13: U55.20, U56.35
RX14: U59.20, U60.35
SCK: J4.11, U5.29
SCK1: J7.11, U8.29
SCK2: J11.11, U12.29
SCK3: J15.11, U16.29
SCK4: J19.11, U20.29
SCK5: J23.11, U24.29
SCK6: J27.11, U28.29
SCK7: J31.11, U32.29
SCK8: J35.11, U36.29
SCK9: J39.11, U40.29
SCK10: J43.11, U44.29
SCK11: J47.11, U48.29
SCK12: J51.11, U52.29
SCK13: J55.11, U56.29
SCK14: J59.11, U60.29
SCL: J2.11, J3.4, U5.36
SCL1: J1.4, J6.11, U8.36
SCL2: J9.4, J10.11, U12.36
SCL3: J13.4, J14.11, U16.36
SCL4: J17.4, J18.11, U20.36
SCL5: J21.4, J22.11, U24.36
SCL6: J25.4, J26.11, U28.36
SCL7: J29.4, J30.11, U32.36
SCL8: J33.4, J34.11, U36.36
SCL9: J37.4, J38.11, U40.36
SCL10: J41.4, J42.11, U44.36
SCL11: J45.4, J46.11, U48.36
SCL12: J49.4, J50.11, U52.36
SCL13: J53.4, J54.11, U56.36
SCL14: J57.4, J58.11, U60.36
SDA: J2.12, J3.3, U5.37
SDA1: J1.3, J6.12, U8.37
SDA2: J9.3, J10.12, U12.37
SDA3: J13.3, J14.12, U16.37
SDA4: J17.3, J18.12, U20.37
SDA5: J21.3, J22.12, U24.37
SDA6: J25.3, J26.12, U28.37
SDA7: J29.3, J30.12, U32.37
SDA8: J33.3, J34.12, U36.37
SDA9: J37.3, J38.12, U40.37
SDA10: J41.3, J42.12, U44.37
SDA11: J45.3, J46.12, U48.37
SDA12: J49.3, J50.12, U52.37
SDA13: J53.3, J54.12, U56.37
SDA14: J57.3, J58.12, U60.37
TX: U4.21, U5.34
TX1: U7.21, U8.34
TX2: U11.21, U12.34
TX3: U15.21, U16.34
TX4: U19.21, U20.34
TX5: U23.21, U24.34
TX6: U27.21, U28.34
TX7: U31.21, U32.34
TX8: U35.21, U36.34
TX9: U39.21, U40.34
TX10: U43.21, U44.34
TX11: U47.21, U48.34
TX12: U51.21, U52.34
TX13: U55.21, U56.34
TX14: U59.21, U60.34
VIN: C7.1, D2.C, Q1.2, R8.1, U3.1
VIN1: C4.1, D4.C, Q3.2, R20.1, U6.1
VIN2: C14.1, D7.C, Q5.2, R31.1, U10.1
VIN3: C22.1, D10.C, Q7.2, R42.1, U14.1
VIN4: C29.1, D13.C, Q9.2, R53.1, U18.1
VIN5: C36.1, D16.C, Q11.2, R64.1, U22.1
VIN6: C43.1, D19.C, Q13.2, R75.1, U26.1
VIN7: C50.1, D22.C, Q15.2, R86.1, U30.1
VIN8: C57.1, D25.C, Q17.2, R97.1, U34.1
VIN9: C64.1, D28.C, Q19.2, R108.1, U38.1
VIN10: C71.1, D31.C, Q21.2, R119.1, U42.1
VIN11: C78.1, D34.C, Q23.2, R130.1, U46.1
VIN12: C85.1, D37.C, Q25.2, R141.1, U50.1
VIN13: C92.1, D40.C, Q27.2, R152.1, U54.1
VIN14: C99.1, D43.C, Q29.2, R163.1, U58.1
V_BATT: C6.1, J2.1, JP2.2, Q1.3, U1.3
V_BATT1: C8.1, J6.1, JP1.2, Q3.3, U2.3
V_BATT2: C16.1, J10.1, JP3.2, Q5.3, U9.3
V_BATT3: C24.1, J14.1, JP4.2, Q7.3, U13.3
V_BATT4: C31.1, J18.1, JP5.2, Q9.3, U17.3
V_BATT5: C38.1, J22.1, JP6.2, Q11.3, U21.3
V_BATT6: C45.1, J26.1, JP7.2, Q13.3, U25.3
V_BATT7: C52.1, J30.1, JP8.2, Q15.3, U29.3
V_BATT8: C59.1, J34.1, JP9.2, Q17.3, U33.3
V_BATT9: C66.1, J38.1, JP10.2, Q19.3, U37.3
V_BATT10: C73.1, J42.1, JP11.2, Q21.3, U41.3
V_BATT11: C80.1, J46.1, JP12.2, Q23.3, U45.3
V_BATT12: C87.1, J50.1, JP13.2, Q25.3, U49.3
V_BATT13: C94.1, J54.1, JP14.2, Q27.3, U53.3
V_BATT14: C101.1, J58.1, JP15.2, Q29.3, U57.3
V_USB: C19.1, D2.A, J2.3, J5.VBUS, Q1.1, R3.1, R5.2, R7.2, U1.4
V_USB1: C9.1, D4.A, J6.3, J8.VBUS, Q3.1, R10.2, R11.1, R21.2, U2.4
V_USB2: C17.1, D7.A, J10.3, J12.VBUS, Q5.1, R23.2, R24.1, R32.2, U9.4
V_USB3: C25.1, D10.A, J14.3, J16.VBUS, Q7.1, R34.2, R35.1, R43.2, U13.4
V_USB4: C32.1, D13.A, J18.3, J20.VBUS, Q9.1, R45.2, R46.1, R54.2, U17.4
V_USB5: C39.1, D16.A, J22.3, J24.VBUS, Q11.1, R56.2, R57.1, R65.2, U21.4
V_USB6: C46.1, D19.A, J26.3, J28.VBUS, Q13.1, R67.2, R68.1, R76.2, U25.4
V_USB7: C53.1, D22.A, J30.3, J32.VBUS, Q15.1, R78.2, R79.1, R87.2, U29.4
V_USB8: C60.1, D25.A, J34.3, J36.VBUS, Q17.1, R89.2, R90.1, R98.2, U33.4
V_USB9: C67.1, D28.A, J38.3, J40.VBUS, Q19.1, R100.2, R101.1, R109.2, U37.4
V_USB10: C74.1, D31.A, J42.3, J44.VBUS, Q21.1, R111.2, R112.1, R120.2, U41.4
V_USB11: C81.1, D34.A, J46.3, J48.VBUS, Q23.1, R122.2, R123.1, R131.2, U45.4
V_USB12: C88.1, D37.A, J50.3, J52.VBUS, Q25.1, R133.2, R134.1, R142.2, U49.4
V_USB13: C95.1, D40.A, J54.3, J56.VBUS, Q27.1, R144.2, R145.1, R153.2, U53.4
V_USB14: C102.1, D43.A, J58.3, J60.VBUS, Q29.1, R155.2, R156.1, R164.2, U57.4

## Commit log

2020-10-09 starting from 32d version, local libarary work done
2020-10-09 switched to u.fl module and modified the CP2104 VBUS input
    -u.fl module swapped out
    -added standoffs and new measures
    -moved product name and logo to top of board
    -added in voltage split circuit to vbus input to CP2104
    -connected VREGIN pin on CP2104 to 3.3V (previously was connected to vbus)
    -changed value of R1 to 2.2K
2020-10-13 post design review changes
    -changed R1 to a 10K (pullup on RSTB on CP2102)
    -nudged U1 (and nearby passives) down to make more space around pin 13 LED.
    -changed all 0402 "standard" footprints to use the "tight". re-routed as necessary.
    -made all 4.7uF caps the same 0402 part
    -made all 1.0uF caps (qty 2) the same 0402 part (X5R)
2020-10-13 new buzzards, swapped out Miso/Mosi naming
2020-10-14 aesthetic changes from post review review
    -Change CIPO and COPI pin names in symbol to SDI/SDO
    -Updated product name bottom silk to include "32"
    -Removed extra top silk flame logo at bottom right (since we had room for the full name and flame logo at the top.
    -changed silk names for DI/DO to SDI/SDO for more consitency in schematic/board naming.
2020-10-14 Run of checklist catches
    -vector font in sch
    -flag label on NET "0"
    -changes top silk on RST pin to include active low marking
2020-10-15 changing library part names/descriptions to the 32EU
2020-10-15 updated ESP32EU footprint to match gnd pad array from datasheet
    -also added gnd pours to top and bottom copper
2020-10-16 Increased top and bottom ground pour isolate to 0.01"
    This provides more clearance and prevents the tStop (mask opening) from exposing any nearby ground pour.
2020-10-16 removed dimension of module that was accidentally on tPlace
2020-10-16 Production panel and gerbers v10
2021-08-11 Silk Update
    Updated silk on bottom
    Added "Doot" to GPIO0 button
2023-02-10 Update Datasheet
